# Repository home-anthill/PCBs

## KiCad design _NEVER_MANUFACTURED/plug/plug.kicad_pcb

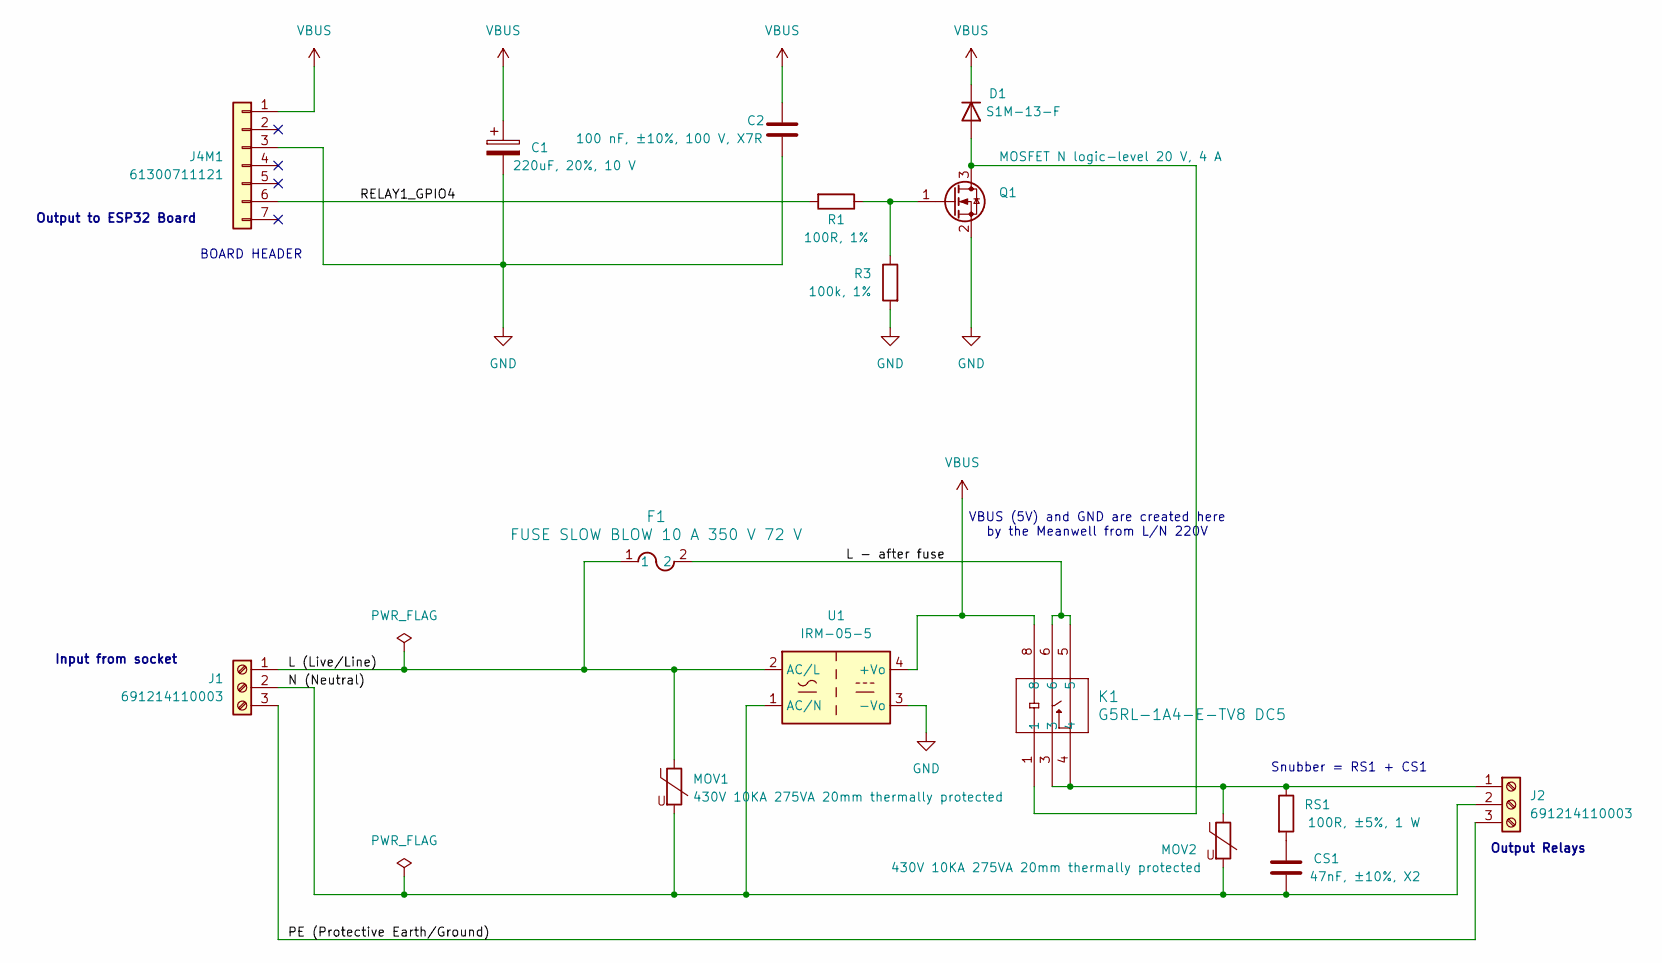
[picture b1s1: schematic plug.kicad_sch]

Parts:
C1: 220uF, 20%, 10 V; CP_Radial_D5.0mm_P2.00mm; MPN EEU-FR1A221B; Digi-Key Part Number P15322CT-ND
C2: 100 nF, ±10%, 100 V, X7R; C_0603_1608Metric; MPN GRM188R72A104KA35D; Digi-Key Part Number 490-3285-1-ND
CS1: 47nF, ±10%, X2; C_Rect_L13.0mm_W5.0mm_P10.00mm_FKS3_FKP3_MKS4; MPN B32921C3473K000; Digi-Key Part Number 495-6903-ND
D1: S1M-13-F; D_SMA; MPN S1M-13-F; Digi-Key Part Number S1M-FDICT-ND
F1: FUSE SLOW BLOW 10 A 350 V 72 V; Bel_fuse_0697H9100-01; MPN 0697H9100-01; Digi-Key Part Number 5923-0697H9100-01-ND
J1, J2: 691214110003; Wurth_WR-TBL_691214110003; MPN 691214110003; Digi-Key Part Number 732-2748-ND
J4M1: 61300711121; PinHeader_1x07_P2.54mm_Vertical; MPN 61300711121; Digi-Key Part Number 732-5320-ND
K1: G5RL-1A4-E-TV8 DC5; G5RL-1A-E-TV8 DC5; MPN G5RL-1A4-E-TV8 DC5; Digi-Key Part Number Z6076-ND
MOV1, MOV2: 430V 10KA 275VA 20mm thermally protected; Eaton_MOVTP20V275N; MPN MOVTP20V275N; Digi-Key Part Number 283-MOVTP20V275N-ND
Q1: MOSFET N logic-level 20 V, 4 A; SOT-23; MPN DMN2056U-7; Digi-Key Part Number DMN2056U-7DICT-ND
R1: 100R, 1%; R_0603_1608Metric; MPN RC0603FR-07100RL; Digi-Key Part Number 311-100HRCT-ND
R3: 100k, 1%; R_0603_1608Metric; MPN RC0603FR-07100KL; Digi-Key Part Number 311-100KHRCT-ND
RS1: 100R, ±5%, 1 W; R_Axial_DIN0614_L14.3mm_D5.7mm_P20.32mm_Horizontal; MPN AC01000001000JACCS; Digi-Key Part Number BC3224CT-ND
U1: IRM-05-5; Converter_ACDC_MeanWell_IRM-05-xx_THT; MPN IRM-05-5; Digi-Key Part Number 1866-3027-ND

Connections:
/L (Live/Line): F1.1, J1.1, MOV1.1, U1.2 (AC/L)
/L - after fuse: F1.2, K1.5, K1.6
/N (Neutral): CS1.2, J1.2, J2.2, MOV1.2, MOV2.2, U1.1 (AC/N)
/PE (Protective Earth/Ground): J1.3, J2.3
/RELAY1_GPIO4: J4M1.6, R1.2
GND: C1.2, C2.2, J4M1.3, Q1.2 (S), R3.2, U1.3 (-Vo)
unnamed: CS1.1, RS1.2
unnamed: D1.2 (A), K1.1, Q1.3 (D)
unnamed: J2.1, K1.3, K1.4, MOV2.1, RS1.1
unnamed: Q1.1 (G), R1.1, R3.1
VBUS: C1.1, C2.1, D1.1 (K), J4M1.1, K1.8, U1.4 (+Vo)

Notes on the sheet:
VBUS (5V) and GND are created here by the Meanwell from L/N 220V
Output to ESP32 Board
Input from socket
BOARD HEADER
Snubber = RS1 + CS1
Output Relays

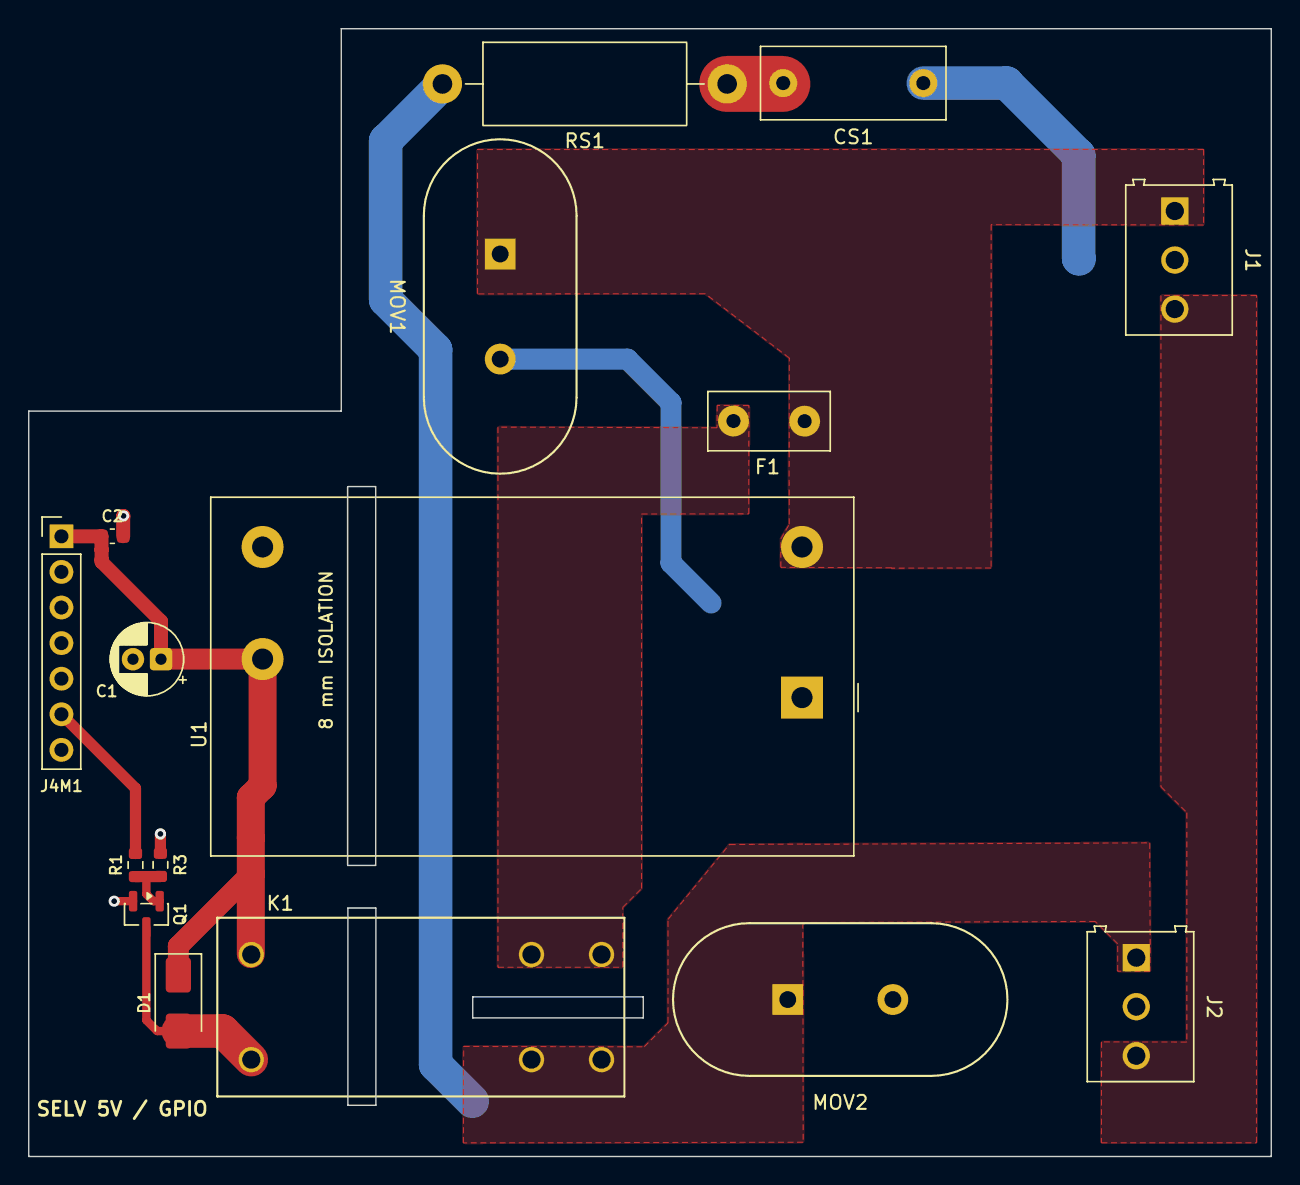
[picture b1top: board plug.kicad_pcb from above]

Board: 2 copper layers, 88.7 x 80.5 mm, 16 parts (0 on the bottom side), 11 nets.

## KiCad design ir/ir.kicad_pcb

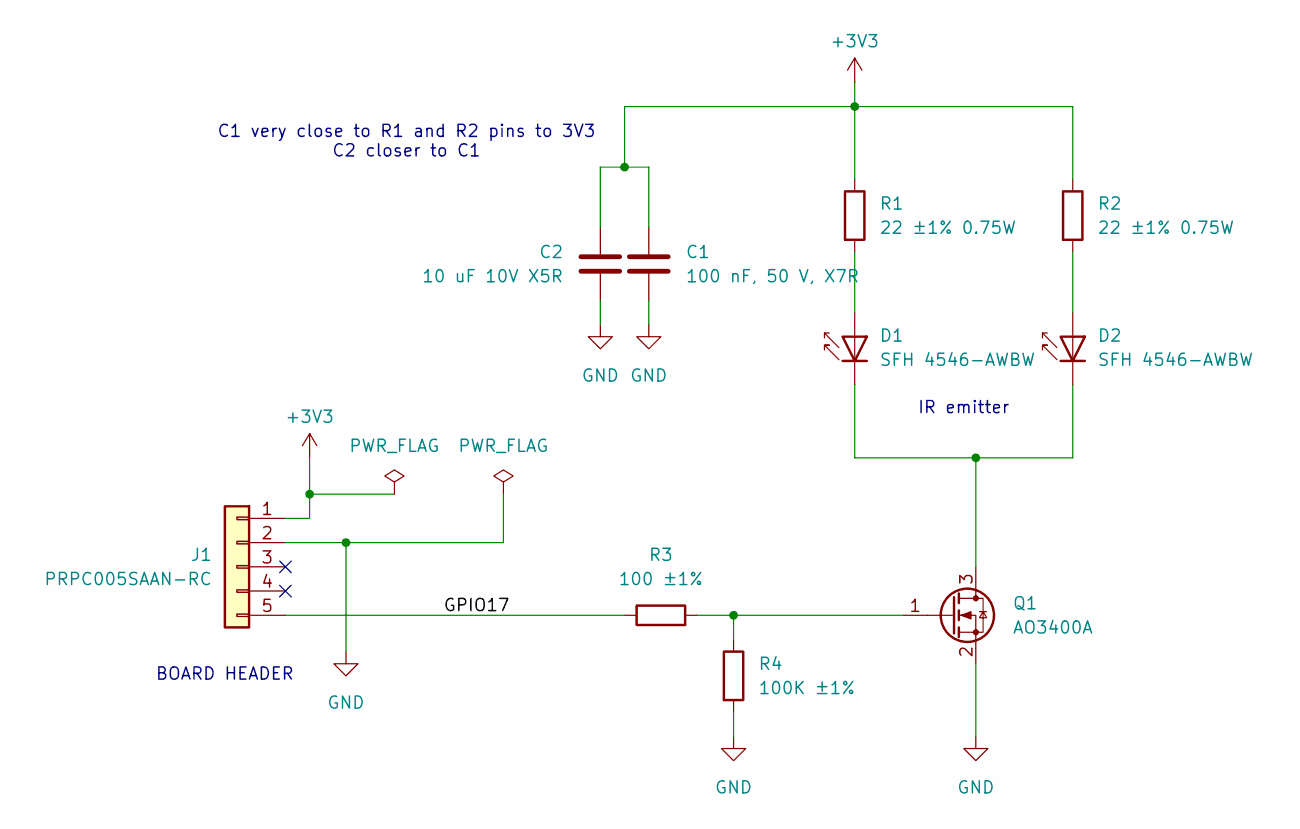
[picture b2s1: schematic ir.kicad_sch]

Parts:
C1: 100 nF, 50 V, X7R; C_0603_1608Metric; MPN C0603C104K5RACTU; Digi-Key Part Number 399-C0603C104K5RACTUCT-ND
C2: 10 uF 10V X5R; C_0805_2012Metric; MPN C0805C106K8PACTU; Digi-Key Part Number 399-C0805C106K8PACTUCT-ND
D1, D2: SFH 4546-AWBW; LED_D5.0mm; MPN SFH 4546-AWBW; Digi-Key Part Number 475-SFH4546-AWBW-ND
J1: PRPC005SAAN-RC; PinHeader_1x05_P2.54mm_Vertical; MPN PRPC005SAAN-RC; Digi-Key Part Number 35-PRPC005SAAN-RC-ND
Q1: AO3400A; SOT-23; MPN AO3400A; Digi-Key Part Number 785-1000-1-ND
R1, R2: 22 ±1% 0.75W; R_1206_3216Metric; MPN CRCW120622R0FKEAHP; Digi-Key Part Number 541-22.0UCT-ND
R3: 100 ±1%; R_0603_1608Metric; MPN RC0603FR-07100RL; Digi-Key Part Number 311-100HRCT-ND
R4: 100K ±1%; R_0603_1608Metric; MPN RC0603FR-07100KL; Digi-Key Part Number 311-100KHRCT-ND

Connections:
+3V3: C1.1, C2.1, J1.1, R1.1, R2.1
/GPIO17: J1.5, R3.1
GND: C1.2, C2.2, J1.2, Q1.2 (S), R4.2
unnamed: D1.2 (A), R1.2
unnamed: D1.1 (K), D2.1 (K), Q1.3 (D)
unnamed: D2.2 (A), R2.2
unnamed: Q1.1 (G), R3.2, R4.1

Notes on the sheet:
IR emitter
C1 very close to R1 and R2 pins to 3V3 C2 closer to C1
BOARD HEADER

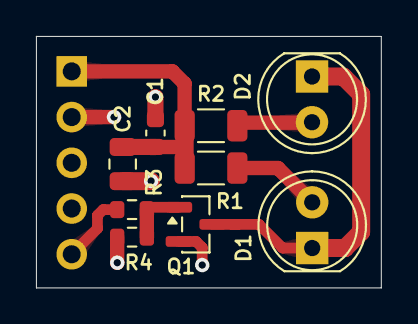
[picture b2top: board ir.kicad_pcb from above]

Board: 2 copper layers, 19.2 x 14.0 mm, 10 parts (1 on the bottom side), 7 nets.

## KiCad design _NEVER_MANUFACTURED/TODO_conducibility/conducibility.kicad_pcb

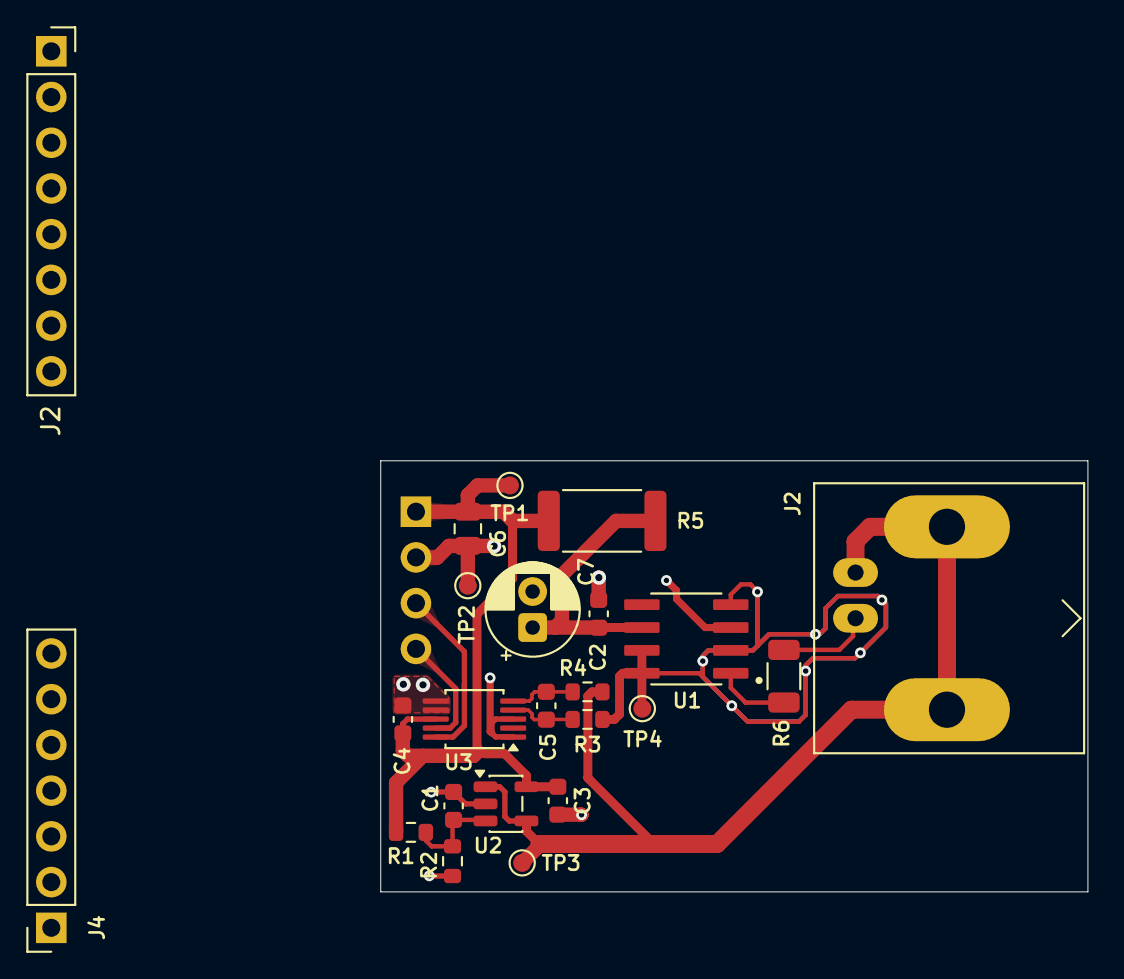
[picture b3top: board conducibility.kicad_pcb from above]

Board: 2 copper layers, 39.3 x 24.0 mm, 24 parts (1 on the bottom side), 15 nets.

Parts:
C1: 1 uF, X5R; C_0603_1608Metric
C2, C3: 100 nF, X7R; C_0603_1608Metric
C4, C5: 100 nF, 16 V, X7R, ±10%; C_0603_1608Metric
C6: 10 uF, 16 V, X6S, ±10%; C_0805_2012Metric
C7: 100 uF; CP_Radial_D5.0mm_P2.00mm
J1: PRPC004SAAN-RC; PinHeader_1x04_P2.54mm_Vertical
J2: Female BNC; BNC_Amphenol_B6252HB-NPP3G-50_Horizontal
J2#2: PPTC081LFBN-RC; PinSocket_1x08_P2.54mm_Vertical
J4: PPTC071LFBN-RC; PinSocket_1x07_P2.54mm_Vertical
R1, R2: 10 k; R_0603_1608Metric
R3, R4: 1 k; R_0603_1608Metric
R5: 22, 1%; R_2512_6332Metric
R6: 10 k, 1%; R_1206_3216Metric
TP1: TP 3V3; TestPoint_Pad_D1.0mm
TP2: TP GND; TestPoint_Pad_D1.0mm
TP3: TP VBIAS; TestPoint_Pad_D1.0mm
TP4: TP ph out; TestPoint_Pad_D1.0mm
U1: LMP7721MA_NOPB; SOIC127P599X175-8N
U2: OPA333; SOT-23-5
U3: ADS1115, ADC I²C; TSSOP-10_3x3mm_P0.5mm

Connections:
+3V3: C3.1, C4.1, C6.1, J1.1, J2#2.1, J4.6, R1.1, R5.1, TP1.1 (1_1), U2.5 (V+), U3.8 (VDD)
/ADC_PH_N: C5.2, R4.2, U3.5 (AIN1)
/ADC_PH_P: C5.1, R3.2, U3.4 (AIN0)
/PH_BUF: R3.1, TP4.1 (1_1), U1.2 (N/C_2), U1.4, U1.7 (N/C_7), U1.8
/PH_IN: J2.1 (In), R6.2
/PH_SENSE: R6.1, U1.1
/SCL: J1.3, U3.10 (SCL)
/SDA: J1.4, U3.9 (SDA)
/VBIAS: J2.2 (Ext), R4.1, TP3.1 (1_1), U2.1, U2.4 (-)
/VDD_PH: C2.1, C7.1, R5.2, U1.6
/VMID_RAW: C1.1, R1.2, R2.1, U2.3 (+)
GND: C1.2, C2.2, C3.2, C4.2, C6.2, C7.2, J1.2, J2#2.2, J4.5, R2.2, TP2.1 (1_1), U1.3, U2.2 (V-), U3.1 (ADDR), U3.3 (GND), U3.6 (AIN2), U3.7 (AIN3)
GPIO4: J2#2.3, J4.1
GPIO5: J2#2.4, J4.2
VBUS: J2#2.8, J4.7

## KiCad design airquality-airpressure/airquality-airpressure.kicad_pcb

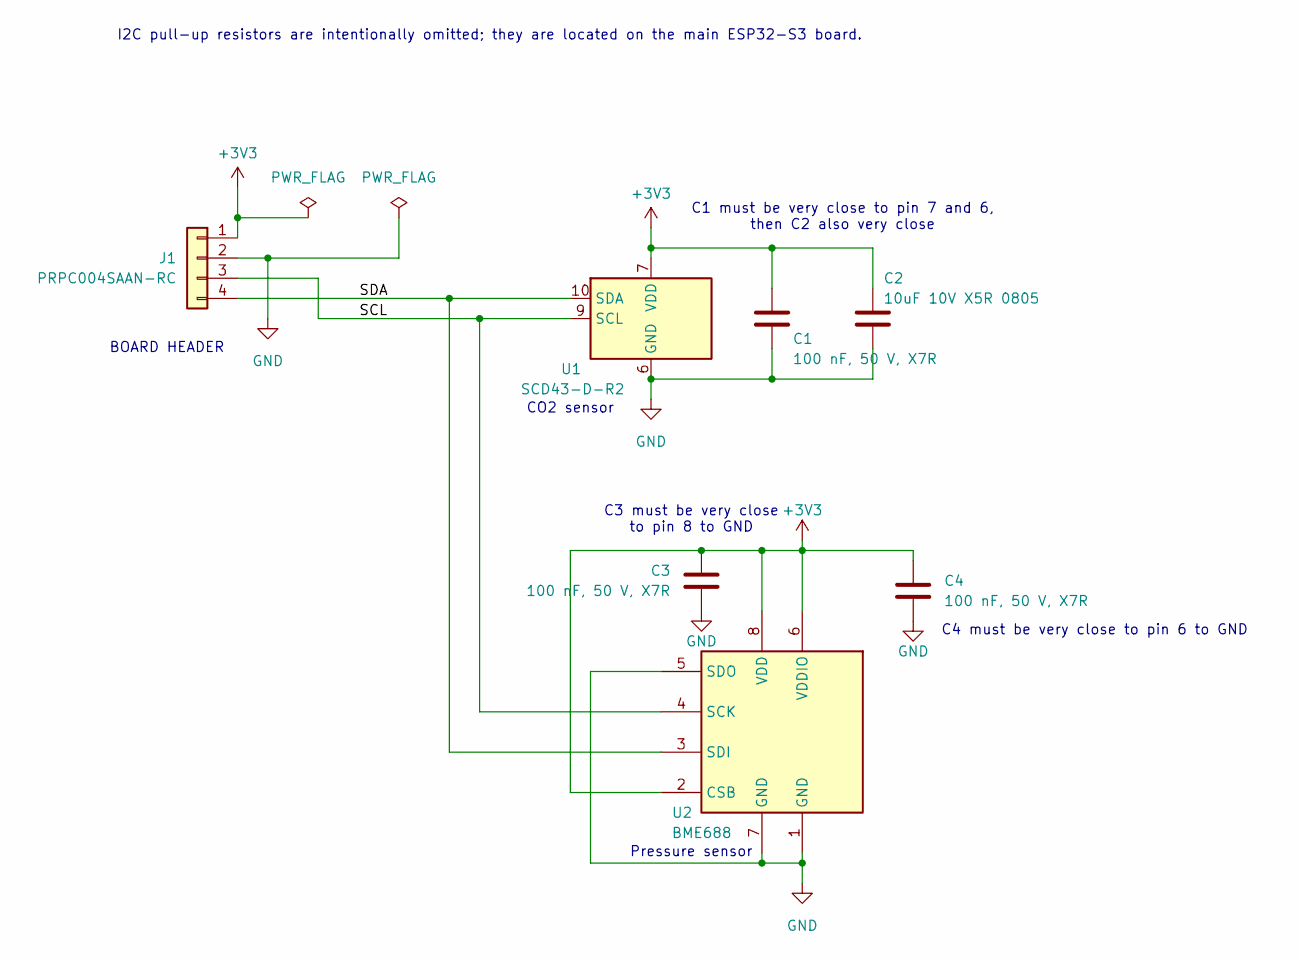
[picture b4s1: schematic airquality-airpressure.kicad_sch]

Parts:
C1, C3, C4: 100 nF, 50 V, X7R; C_0603_1608Metric; MPN C0603C104K5RACTU; Digi-Key Part Number 399-C0603C104K5RACTUCT-ND
C2: 10uF 10V X5R 0805; C_0805_2012Metric; MPN C0805C106K8PACTU; Digi-Key Part Number 399-C0805C106K8PACTUCT-ND
J1: PRPC004SAAN-RC; PinHeader_1x04_P2.54mm_Vertical; MPN PRPC004SAAN-RC; Digi-Key Part Number 35-PRPC004SAAN-RC-ND
U1: SCD43-D-R2; Sensirion_SCD4x-1EP_10.1x10.1mm_P1.25mm_EP4.8x4.8mm; MPN SCD43-D-R2; Digi-Key Part Number 1649-SCD43-D-R2CT-ND
U2: BME688; Bosch_LGA-8_3x3mm_P0.8mm_ClockwisePinNumbering; MPN BME688; Digi-Key Part Number 828-BME688CT-ND

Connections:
+3V3: C1.1, C2.1, C3.1, C4.1, J1.1, U1.7 (VDD), U1.19 (VDD), U2.2 (CSB), U2.6 (VDDIO), U2.8 (VDD)
/SCL: J1.3, U1.9 (SCL), U2.4 (SCK)
/SDA: J1.4, U1.10 (SDA), U2.3 (SDI)
GND: C1.2, C2.2, C3.2, C4.2, J1.2, U1.6 (GND), U1.20 (GND), U1.21 (GND), U2.1 (GND), U2.5 (SDO), U2.7 (GND)

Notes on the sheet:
I2C pull-up resistors are intentionally omitted; they are located on the main ESP32-S3 board.
C3 must be very close to pin 8 to GND
C4 must be very close to pin 6 to GND
CO2 sensor
BOARD HEADER
Pressure sensor
C1 must be very close to pin 7 and 6, then C2 also very close

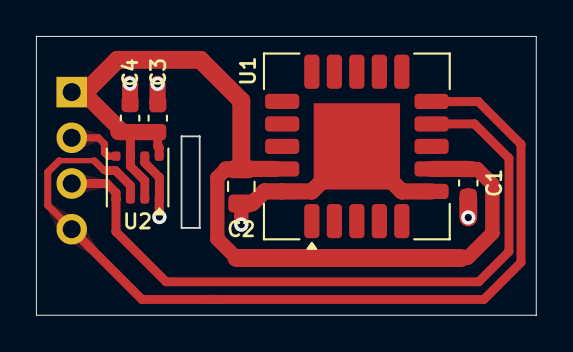
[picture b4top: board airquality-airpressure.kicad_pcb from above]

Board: 2 copper layers, 27.8 x 15.5 mm, 7 parts (1 on the bottom side), 4 nets.

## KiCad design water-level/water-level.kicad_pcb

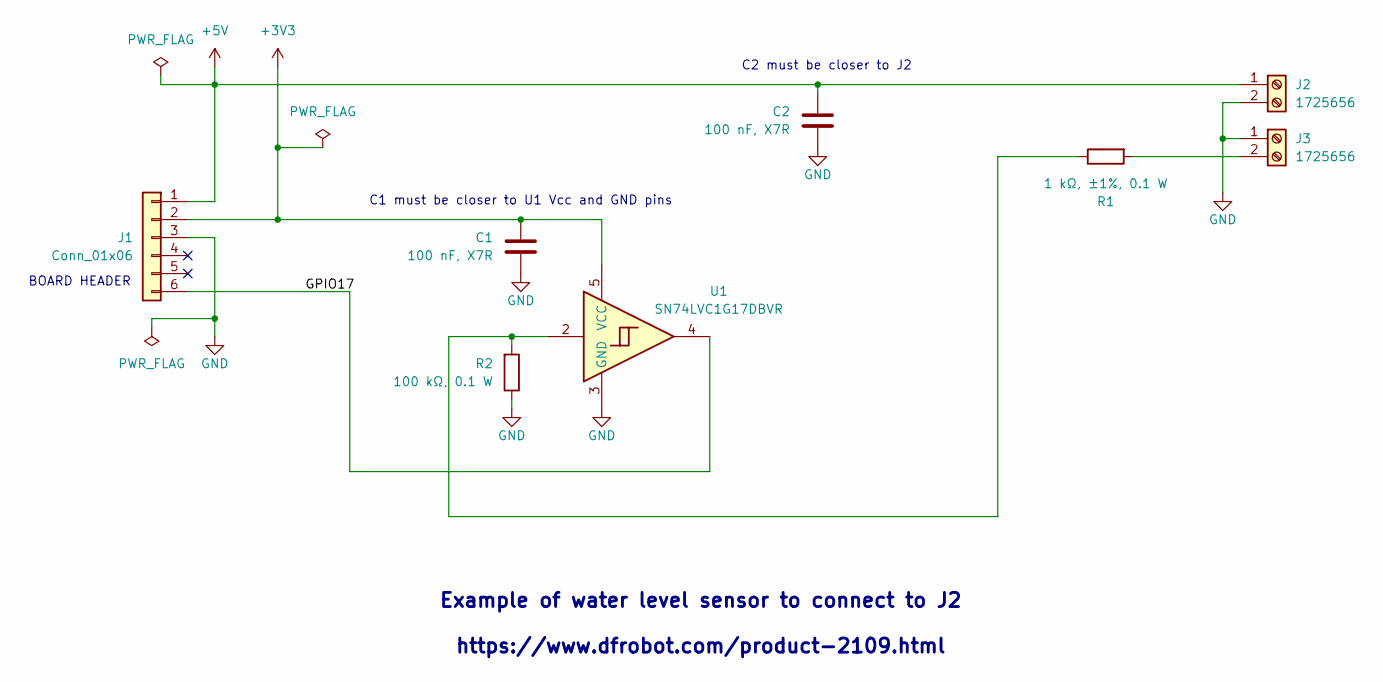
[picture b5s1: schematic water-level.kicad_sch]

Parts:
C1, C2: 100 nF, X7R; C_0603_1608Metric; MPN CC0603KRX7R9BB104; Digi-Key Part Number 311-1344-1-ND
J1: Conn_01x06; PinHeader_1x06_P2.54mm_Vertical; MPN 61300611121; Digi-Key Part Number 732-5319-ND
J2, J3: 1725656; TerminalBlock_Phoenix_MPT-0,5-2-2.54_1x02_P2.54mm_Horizontal; MPN 1725656; Digi-Key Part Number 277-1273-ND
R1: 1 kΩ, ±1%, 0.1 W; R_0603_1608Metric; MPN RC0603FR-071KL; Digi-Key Part Number 311-1.00KHRCT-ND
R2: 100 kΩ, 0.1 W; R_0603_1608Metric; MPN RC0603FR-07100KL; Digi-Key Part Number 311-100KHRCT-ND
U1: SN74LVC1G17DBVR; SOT-23-5; MPN SN74LVC1G17DBVR; Digi-Key Part Number 296-11933-1-ND

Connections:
+3V3: C1.1, J1.2, U1.5 (VCC)
+5V: C2.1, J1.1, J2.1
/GPIO17: J1.6, U1.4
GND: C1.2, C2.2, J1.3, J2.2, J3.1, R2.1, U1.3 (GND)
unnamed: J3.2, R1.2
unnamed: R1.1, R2.2, U1.2

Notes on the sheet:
C2 must be closer to J2
BOARD HEADER
Example of water level sensor to connect to J2 https://www.dfrobot.com/product-2109.html
C1 must be closer to U1 Vcc and GND pins

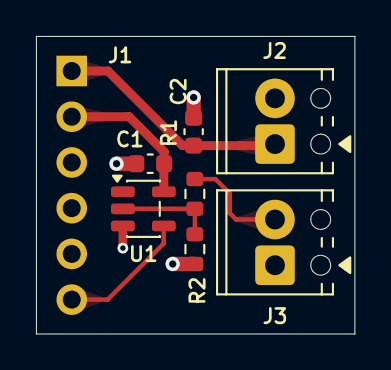
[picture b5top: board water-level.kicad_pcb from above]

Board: 2 copper layers, 17.7 x 16.5 mm, 8 parts (1 on the bottom side), 6 nets.

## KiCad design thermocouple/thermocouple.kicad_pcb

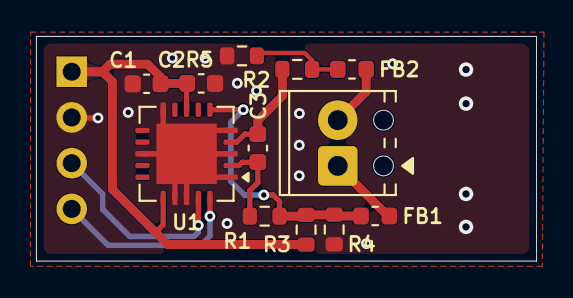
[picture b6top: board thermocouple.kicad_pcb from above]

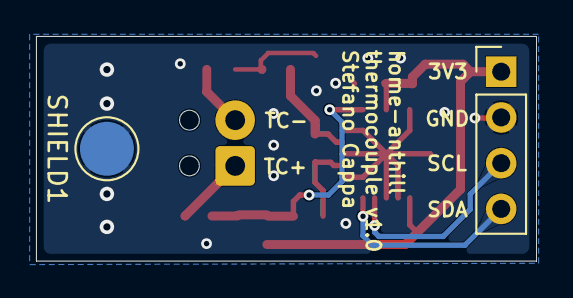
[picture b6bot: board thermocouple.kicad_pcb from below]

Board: 2 copper layers, 27.8 x 12.5 mm, 14 parts (2 on the bottom side), 10 nets.

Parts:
C1, C3: 100 nF, 50 V, X7R; C_0603_1608Metric
C2: 1 uF 10V X5R 0603; C_0603_1608Metric
FB1, FB2: Ferrite 120 Ω @ 100 MHz; L_0603_1608Metric
J1: PRPC004SAAN-RC; PinHeader_1x04_P2.54mm_Vertical
J2: Conn_01x02; TerminalBlock_Phoenix_MPT-0,5-2-2.54_1x02_P2.54mm_Horizontal
R1, R2: 100, ±1%; R_0603_1608Metric
R3: 2 M, ±1%; R_0603_1608Metric
R4: 2,49 M, ±1%; R_0603_1608Metric
R5: 487 k, ±1%; R_0603_1608Metric
SHIELD1: GND shield; TestPoint_Pad_D3.0mm
U1: MCP9601-E/MX; QFN-20-1EP_5x5mm_P0.65mm_EP3.35x3.35mm

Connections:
+3V3: C1.1, C2.1, J1.1, R3.1, U1.8 (V_{DD}), U1.16 (ADDR)
/SCL: J1.3, U1.19 (SCL)
/SDA: J1.4, U1.20 (SDA)
/TC+: FB1.2, J2.1
/TC-: FB2.2, J2.2
/TC_N_ADC: C3.1, R2.1, U1.4 (V_{IN}-)
/TC_N_BIAS: FB2.1, R2.2, R5.1
/TC_P_ADC: C3.2, R1.1, U1.2 (V_{IN}+)
/TC_P_BIAS: FB1.1, R1.2, R3.2, R4.1, U1.6 (V_{SENSE})
GND: C1.2, C2.2, J1.2, R4.2, R5.2, SHIELD1.1 (1_1), U1.1 (GND), U1.3 (GND), U1.5 (GND), U1.10 (GND), U1.13 (GND), U1.17 (GND), U1.18 (GND), U1.21 (GND)

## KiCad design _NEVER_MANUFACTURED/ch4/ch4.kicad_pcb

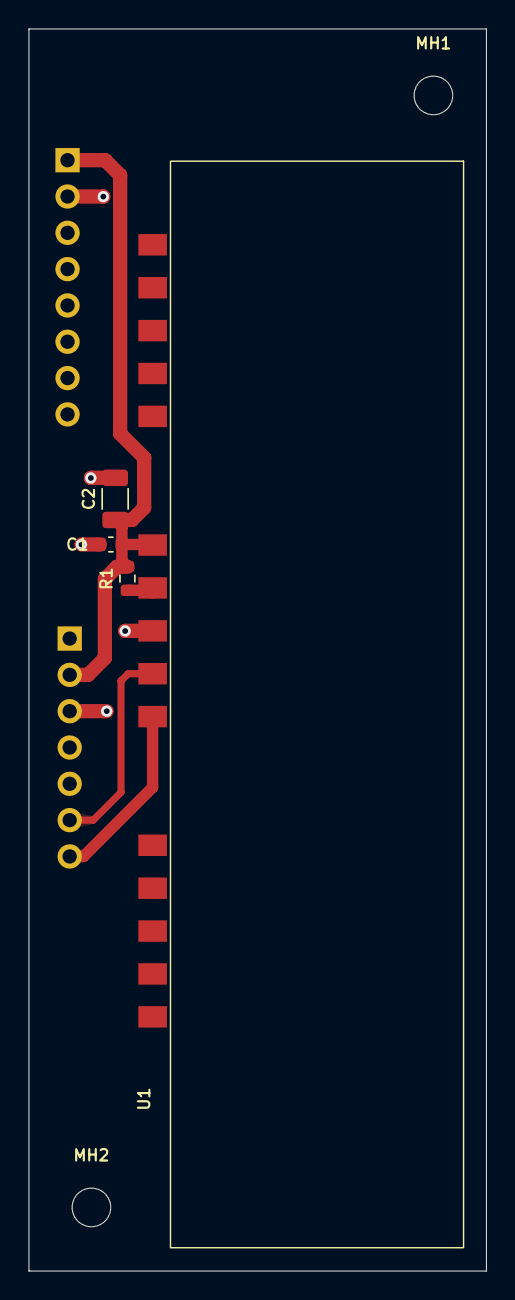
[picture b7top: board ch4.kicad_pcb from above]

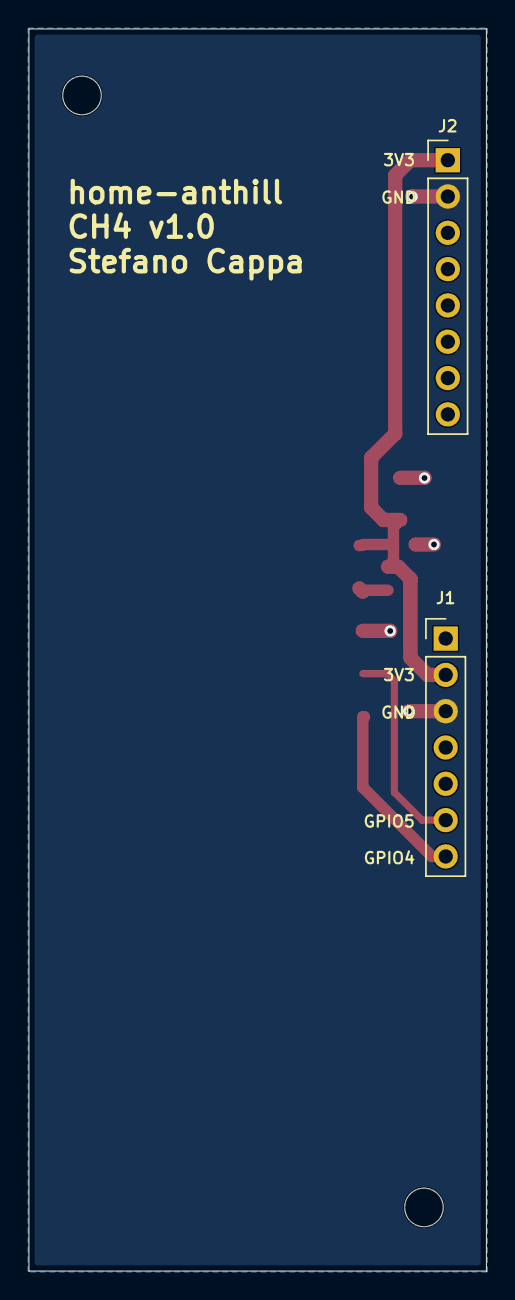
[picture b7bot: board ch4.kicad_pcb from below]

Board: 2 copper layers, 32.0 x 86.9 mm, 8 parts (2 on the bottom side), 5 nets.

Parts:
C1: 100 nF, 50 V, X7R; C_0603_1608Metric
C2: 47uF, 10 V, X5R, ±20%; C_1206_3216Metric
J1: PRPC007SAAN-RC; PinHeader_1x07_P2.54mm_Vertical
J2: PRPC008SAAN-RC; PinHeader_1x08_P2.54mm_Vertical
MH1, MH2: MountingHole; MountingHole_2.7mm_M2.5
R1: 10K, 1%; R_0603_1608Metric
U1: MH-Z9041A

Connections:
+3V3: C1.1, C2.1, J1.2, J2.1, R1.1, U1.6 (VCC)
/RX_GPIO17: J1.6, U1.9 (TXD)
/TX_GPIO16: J1.7, U1.10 (RXD)
GND: C1.2, C2.2, J1.3, J2.2, U1.8 (GND)
unnamed: R1.2, U1.7 (RESET)

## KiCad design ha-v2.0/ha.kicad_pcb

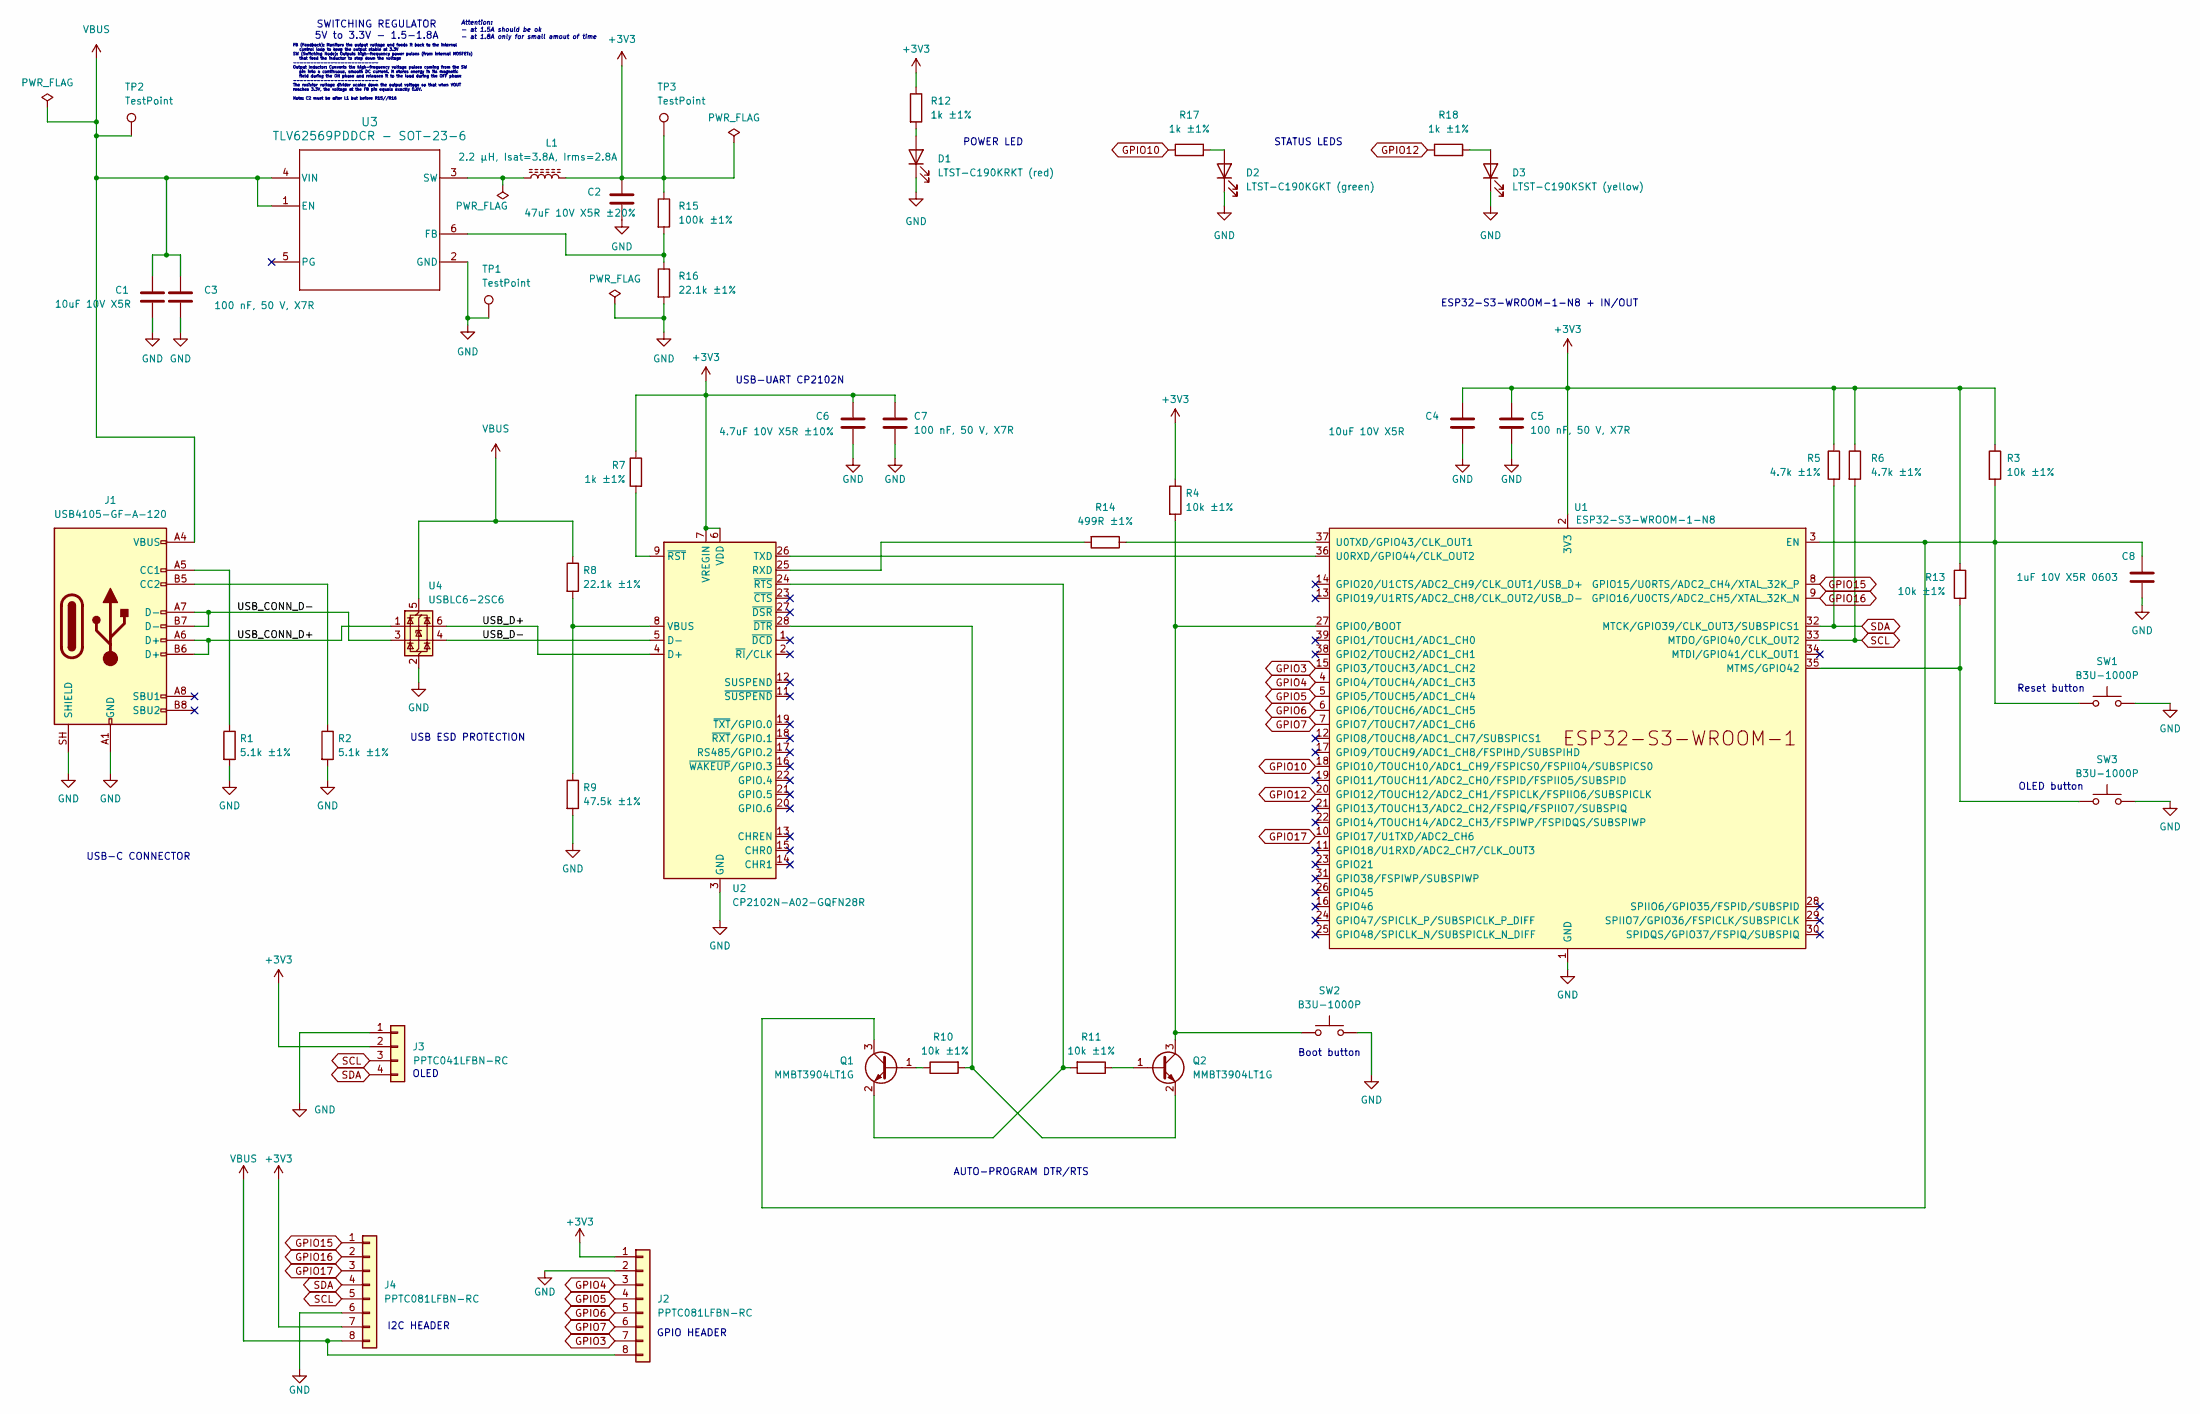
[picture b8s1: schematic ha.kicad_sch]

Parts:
C1, C4: 10uF 10V X5R; C_0805_2012Metric; MPN C0805C106K8PACTU; Digi-Key Part Number 399-C0805C106K8PACTUCT-ND
C2: 47uF 10V X5R ±20%; C_1206_3216Metric; MPN GRM31CR61A476ME15L; Digi-Key Part Number 490-5528-1-ND
C3, C5, C7: 100 nF, 50 V, X7R; C_0603_1608Metric; MPN C0603C104K5RACTU; Digi-Key Part Number 399-C0603C104K5RACTUCT-ND
C6: 4.7uF 10V X5R ±10%; C_0805_2012Metric; MPN CC0805KKX5R6BB475; Digi-Key Part Number 311-1863-1-ND
C8: 1uF 10V X5R 0603; C_0603_1608Metric; MPN GRM188R61A105KA61D; Digi-Key Part Number 490-1543-1-ND
D1: LTST-C190KRKT (red); LED_0603_1608Metric; MPN LTST-C190KRKT; Digi-Key Part Number 160-1447-1-ND
D2: LTST-C190KGKT (green); LED_0603_1608Metric; MPN LTST-C190KGKT; Digi-Key Part Number 160-1435-1-ND
D3: LTST-C190KSKT (yellow); LED_0603_1608Metric; MPN LTST-C190KSKT; Digi-Key Part Number 160-1437-1-ND
J1: USB4105-GF-A-120; USB_C_Receptacle_GCT_USB4105-xx-A_16P_TopMnt_Horizontal; MPN USB4105-GF-A-120; Digi-Key Part Number 2073-USB4105-GF-A-120CT-ND
J2, J4: PPTC081LFBN-RC; PinSocket_1x08_P2.54mm_Vertical; MPN PPTC081LFBN-RC; Digi-Key Part Number S7006-ND
J3: PPTC041LFBN-RC; PinSocket_1x04_P2.54mm_Vertical; MPN PPTC041LFBN-RC; Digi-Key Part Number S7002-ND
L1: 2.2 µH, Isat=3.8A, Irms=2.8A; L_Taiyo-Yuden_MD-4040; MPN LSDND4040MKT2R2MM; Digi-Key Part Number LSDND4040MKT2R2MMCT-ND
Q1, Q2: MMBT3904LT1G; SOT-23; MPN MMBT3904LT1G; Digi-Key Part Number MMBT3904LT1GOSCT-ND
R1, R2: 5.1k ±1%; R_0603_1608Metric; MPN RC0603FR-075K1L; Digi-Key Part Number 311-5.10KHRCT-ND
R3, R4, R10, R11, R13: 10k ±1%; R_0603_1608Metric; MPN RC0603FR-0710KL; Digi-Key Part Number 311-10.0KHRCT-ND
R5, R6: 4.7k ±1%; R_0603_1608Metric; MPN RC0603FR-074K7L; Digi-Key Part Number 311-4.70KHRCT-ND
R7, R12, R17, R18: 1k ±1%; R_0603_1608Metric; MPN RC0603FR-071KL; Digi-Key Part Number 311-1.00KHRCT-ND
R8, R16: 22.1k ±1%; R_0603_1608Metric; MPN RC0603FR-0722K1L; Digi-Key Part Number 311-22.1KHRCT-ND
R9: 47.5k ±1%; R_0603_1608Metric; MPN RC0603FR-0747K5L; Digi-Key Part Number 311-47.5KHRCT-ND
R14: 499R ±1%; R_0603_1608Metric; MPN RC0603FR-07499RL; Digi-Key Part Number 311-499HRCT-ND
R15: 100k ±1%; R_0603_1608Metric; MPN RC0603FR-07100KL; Digi-Key Part Number 311-100KHRCT-ND
SW1, SW2, SW3: B3U-1000P; SW_SPST_B3U-1000P; MPN B3U-1000P; Digi-Key Part Number SW1020CT-ND
TP1, TP2, TP3: TestPoint; TestPoint_Pad_D1.5mm
U1: ESP32-S3-WROOM-1-N8; ESP32-S3-WROOM-1; MPN ESP32-S3-WROOM-1-N8; Digi-Key Part Number 5407-ESP32-S3-WROOM-1-N8CT-ND
U2: CP2102N-A02-GQFN28R; QFN-28-1EP_5x5mm_P0.5mm_EP3.35x3.35mm; MPN CP2102N-A02-GQFN28R; Digi-Key Part Number 336-5890-1-ND
U3: TLV62569PDDCR - SOT-23-6; DDC0006A_N; MPN TLV62569PDDCR; Digi-Key Part Number 296-48175-1-ND
U4: USBLC6-2SC6; SOT-23-6; MPN USBLC6-2SC6; Digi-Key Part Number 497-5235-1-ND

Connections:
+3V3: C2.1, C4.1, C5.1, C6.1, C7.1, J2.1, J3.2, J4.7, L1.2, R3.1, R4.1, R5.1, R6.1, R7.1, R12.1, R13.1, R15.1, TP3.1 (1_1), U1.2 (3V3), U2.6 (VDD), U2.7 (VREGIN)
/USB_CONN_D+: J1.A6 (D+), J1.B6 (D+), U4.1 (I/O1)
/USB_CONN_D-: J1.A7 (D-), J1.B7 (D-), U4.3 (I/O2)
/USB_D+: U2.4 (D+), U4.6 (I/O1)
/USB_D-: U2.5 (D-), U4.4 (I/O2)
GND: C1.2, C2.2, C3.2, C4.2, C5.2, C6.2, C7.2, C8.2, D1.1 (K), D2.1 (K), D3.1 (K), J1.A1 (GND), J1.A12 (GND), J1.B1 (GND), J1.B12 (GND), J1.SH (SHIELD), J2.2, J3.1, J4.6, R1.2, R2.2, R9.2, R16.2, SW1.2, SW2.2, SW3.2, TP1.1 (1_1), U1.1 (GND), U1.40 (GND), U1.41 (GND), U2.3 (GND), U2.29 (GND), U3.2 (GND), U4.2 (GND)
GPIO3: J2.7, U1.15 (GPIO3/TOUCH3/ADC1_CH2)
GPIO4: J2.3, U1.4 (GPIO4/TOUCH4/ADC1_CH3)
GPIO5: J2.4, U1.5 (GPIO5/TOUCH5/ADC1_CH4)
GPIO6: J2.5, U1.6 (GPIO6/TOUCH6/ADC1_CH5)
GPIO7: J2.6, U1.7 (GPIO7/TOUCH7/ADC1_CH6)
GPIO10: R17.1, U1.18 (GPIO10/TOUCH10/ADC1_CH9/FSPICS0/FSPIIO4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)
GPIO12: R18.1, U1.20 (GPIO12/TOUCH12/ADC2_CH1/FSPICLK/FSPIIO6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)
GPIO15: J4.1, U1.8 (GPIO15/U0RTS/ADC2_CH4/XTAL_32K_P)
GPIO16: J4.2, U1.9 (GPIO16/U0CTS/ADC2_CH5/XTAL_32K_N)
GPIO17: J4.3, U1.10 (GPIO17/U1TXD/ADC2_CH6)
unnamed: D1.2 (A), R12.2
unnamed: D2.2 (A), R17.2
unnamed: D3.2 (A), R18.2
unnamed: J1.A5 (CC1), R1.1
unnamed: J1.B5 (CC2), R2.1
unnamed: Q1.1 (B), R10.1
unnamed: C8.1, Q1.3 (C), R3.2, SW1.1, U1.3 (EN)
unnamed: Q1.2 (E), R11.2, U2.24 (~RTS)
unnamed: Q2.1 (B), R11.1
unnamed: Q2.3 (C), R4.2, SW2.1, U1.27 (GPIO0/BOOT)
unnamed: Q2.2 (E), R10.2, U2.28 (~DTR)
unnamed: R13.2, SW3.1, U1.35 (MTMS/GPIO42)
unnamed: U1.36 (U0RXD/GPIO44/CLK_OUT2), U2.26 (TXD)
unnamed: R14.1, U1.37 (U0TXD/GPIO43/CLK_OUT1)
unnamed: R14.2, U2.25 (RXD)
unnamed: R8.2, R9.1, U2.8 (VBUS)
unnamed: R7.2, U2.9 (~RST)
unnamed: R15.2, R16.1, U3.6 (FB)
unnamed: L1.1, U3.3 (SW)
SCL: J3.3, J4.5, R6.2, U1.33 (MTDO/GPIO40/CLK_OUT2)
SDA: J3.4, J4.4, R5.2, U1.32 (MTCK/GPIO39/CLK_OUT3/SUBSPICS1)
VBUS: C1.1, C3.1, J1.A4 (VBUS), J1.A9 (VBUS), J1.B4 (VBUS), J1.B9 (VBUS), J2.8, J4.8, R8.1, TP2.1 (1_1), U3.1 (EN), U3.4 (VIN), U4.5 (VBUS)

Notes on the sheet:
USB-C CONNECTOR
AUTO-PROGRAM DTR/RTS
OLED
POWER LED
Reset button
FB (Feedback): Monitors the output voltage and feeds it back to the internal control loop to keep the output stable at 3.3V SW (Switching Node): Outputs high-frequency power pulses (from internal MOSFETs) that feed the inductor to step down the voltage ------------------------- Output Inductor: Con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
STATUS LEDS
I2C HEADER
ESP32-S3-WROOM-1-N8 + IN/OUT
GPIO HEADER
Boot button
USB-UART CP2102N
SWITCHING REGULATOR 5V to 3.3V - 1.5-1.8A
OLED button
Attention: - at 1.5A should be ok - at 1.8A only for small amout of time
USB ESD PROTECTION
